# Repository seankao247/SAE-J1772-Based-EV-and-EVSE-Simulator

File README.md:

# still working on it
Referenced from https://github.com/OpenEVSE

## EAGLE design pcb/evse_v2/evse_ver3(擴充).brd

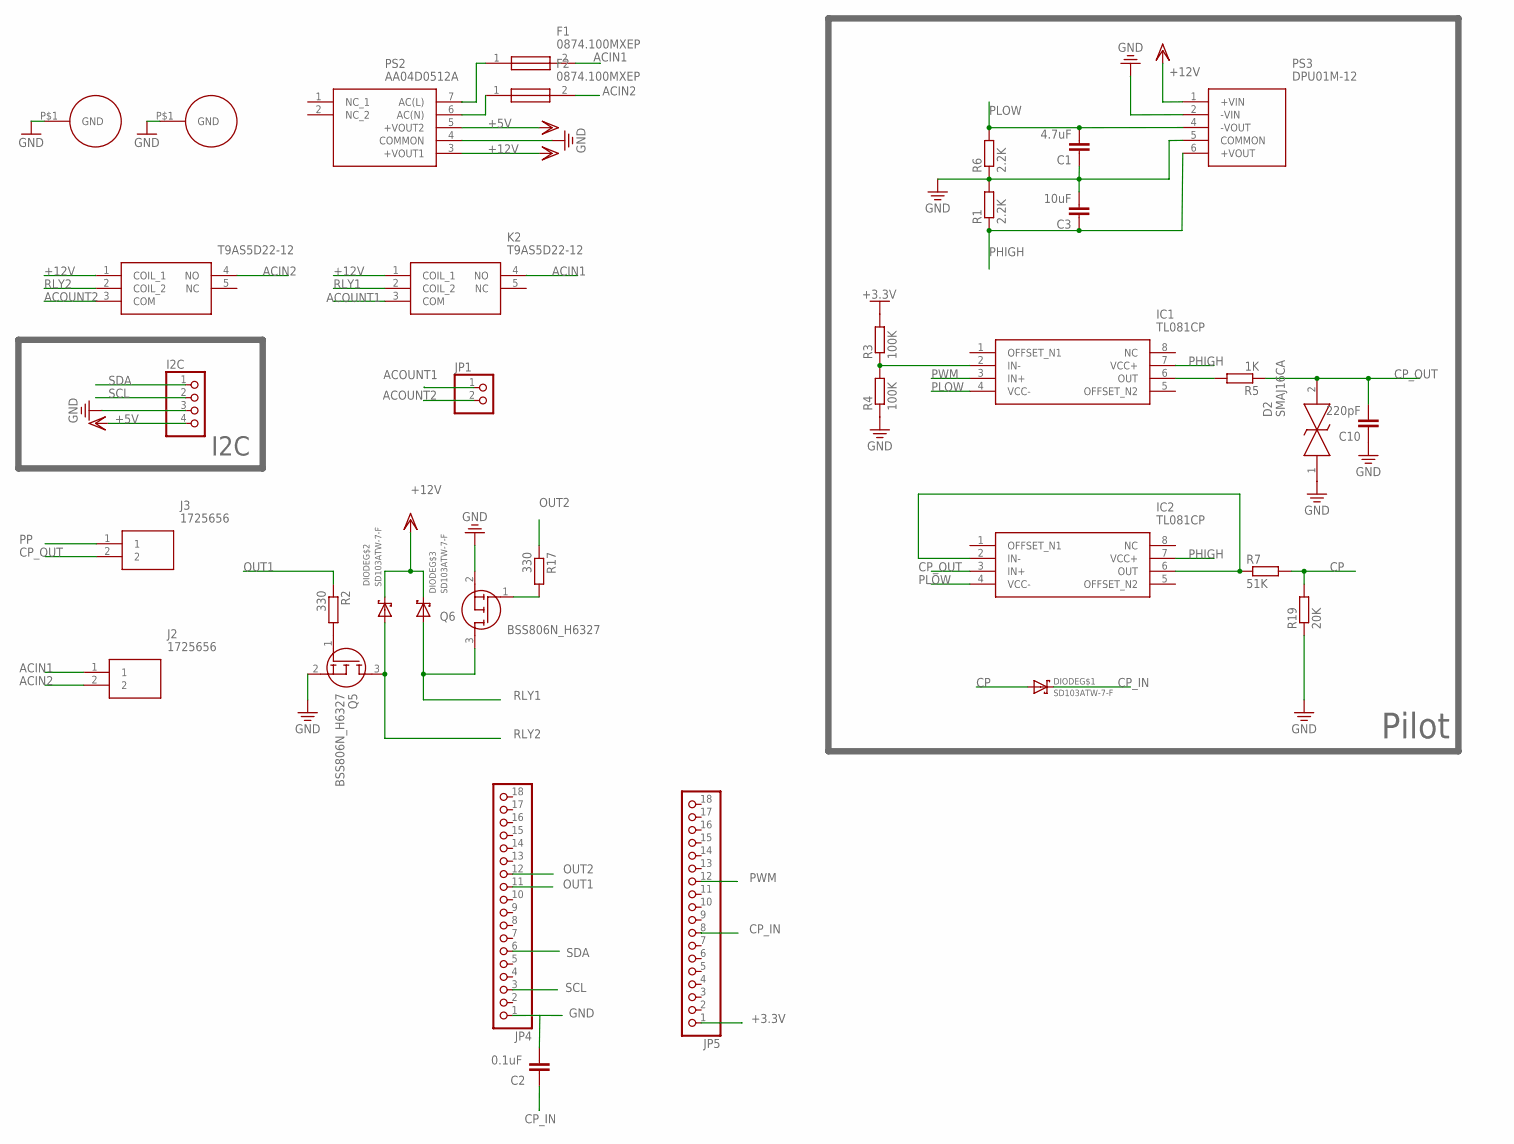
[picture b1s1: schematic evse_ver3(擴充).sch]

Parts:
C1: 4.7uF; C0805
C2: 0.1uF; C0805
C3: 10uF; C0805
C10: 220pF; C0805
D2: SMAJ16CA; DIOM6626X229N
DIODE: SD103ATW-7-F; SOT363
F1, F2: 0874.100MXEP; 0874100MXEP
I2C: PINHD-1X4; 1X04
IC1, IC2: TL081CP; DIP794W53P254L959H508Q8N
J2, J3: 1725656
JP1: PINHD-1X2; 1X02
JP4, JP5: PINHD-1X18; 1X18
K2, K3: T9AS5D22-12; T9AS5D2224314191046
PS2: AA04D0512A
PS3: DPU01M-12; DPU01M12
Q5, Q6: BSS806N_H6327; SOT95P240X110-3N
R1, R6: 2.2K; R0805
R2, R17: 330; R0805
R3, R4: 100K; R0805
R5: 1K; R0805
R7: 51K; R0805
R19: 20K; R0805
U$3, U$4: HOLE

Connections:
+3.3V: JP5.1, R3.2
+5V: I2C.4, PS2.5 (+VOUT2)
+12V: DIODE.2 (C), DIODE.3 (C), K2.1 (COIL_1), K3.1 (COIL_1), PS2.3 (+VOUT1), PS3.1 (+VIN)
ACIN1: F1.2, J2.1, K2.4 (NO)
ACIN2: F2.2, J2.2, K3.4 (NO)
ACOUNT1: JP1.1, K2.3 (COM)
ACOUNT2: JP1.2, K3.3 (COM)
CP: DIODE.6 (A), R7.2, R19.2
CP_IN: C2.1, DIODE.1 (C), JP5.8
CP_OUT: C10.2, D2.2, IC2.3 (IN+), J3.2, R5.1
GND: C1.1, C2.2, C3.2, C10.1, D2.1, I2C.3, JP4.1, PS2.4 (COMMON), PS3.2 (-VIN), PS3.5 (COMMON), Q5.2 (S), Q6.2 (S), R1.2, R4.1, R6.1, R19.1, U$3.P$1, U$4.P$1
unnamed: IC1.2 (IN-), R3.1, R4.2
unnamed: IC1.6 (OUT), R5.2
unnamed: Q5.1 (G), R2.2
unnamed: Q6.1 (G), R17.2
unnamed: IC2.2 (IN-), IC2.6 (OUT), R7.1
unnamed: F2.1, PS2.6 (AC(N))
unnamed: F1.1, PS2.7 (AC(L))
OUT1: JP4.11, R2.1
OUT2: JP4.12, R17.1
PHIGH: C3.1, IC1.7 (VCC+), IC2.7 (VCC+), PS3.6 (+VOUT), R1.1
PLOW: C1.2, IC1.4 (VCC-), IC2.4 (VCC-), PS3.4 (-VOUT), R6.2
PP: J3.1
PWM: IC1.3 (IN+), JP5.12
RLY1: DIODE.4 (A), K2.2 (COIL_2), Q6.3 (D)
RLY2: DIODE.5 (A), K3.2 (COIL_2), Q5.3 (D)
SCL: I2C.2, JP4.3
SDA: I2C.1, JP4.6

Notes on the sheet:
Pilot
I2C

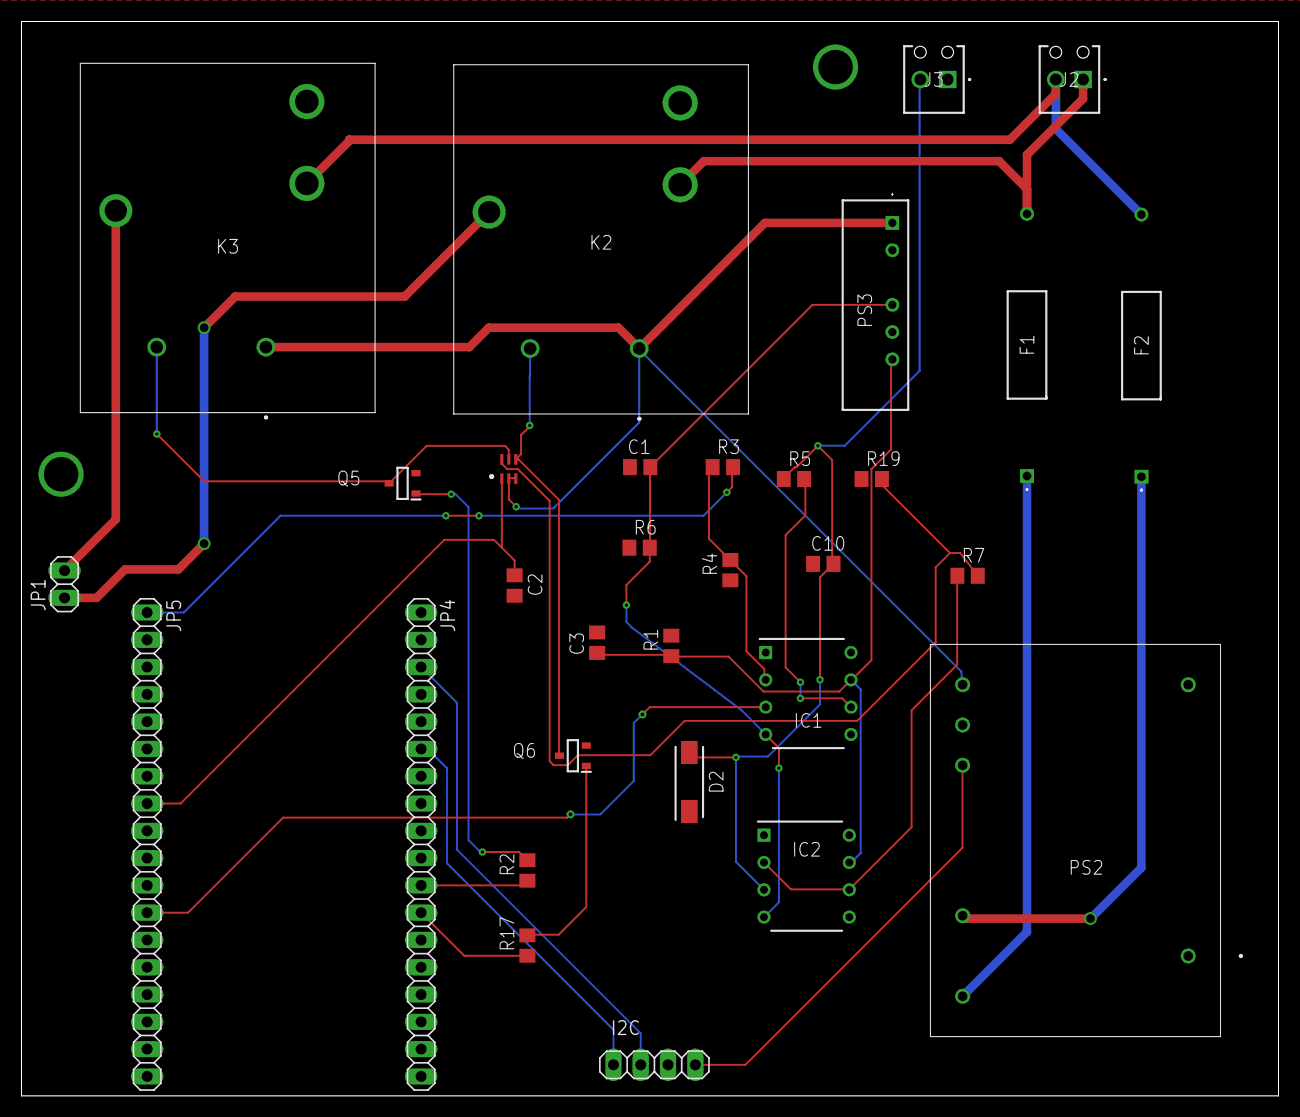
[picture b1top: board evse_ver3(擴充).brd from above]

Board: 2 copper layers, 117.0 x 100.0 mm, 33 parts (0 on the bottom side), 27 nets.

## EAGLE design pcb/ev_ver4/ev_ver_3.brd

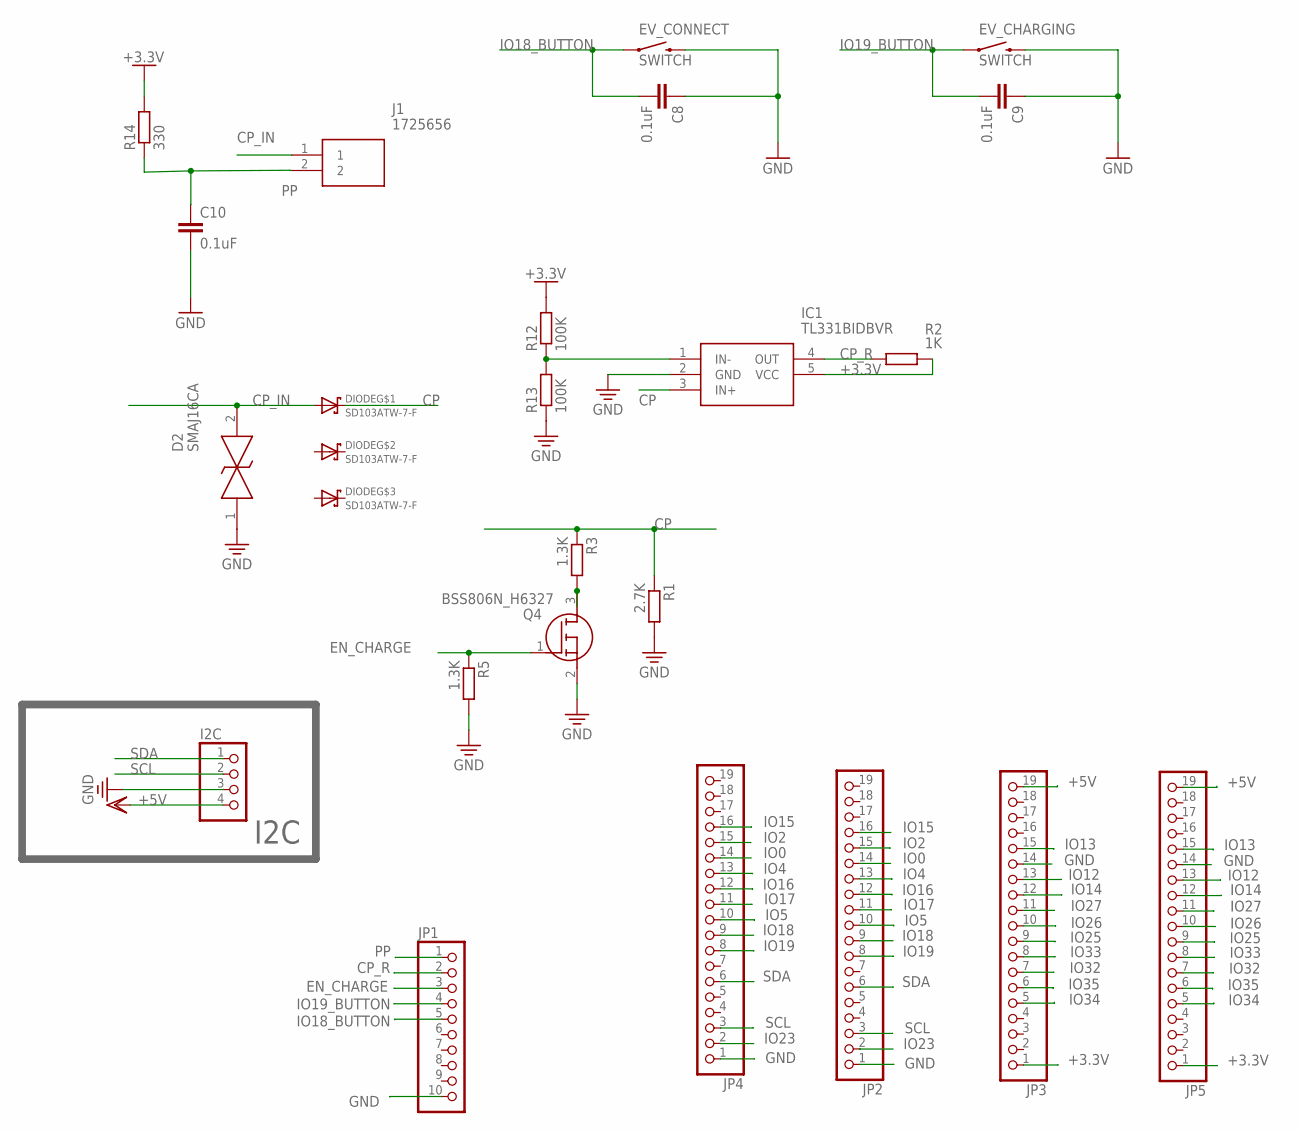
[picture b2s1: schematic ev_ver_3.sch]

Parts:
C8, C9, C10: 0.1uF; C0805
D2: SMAJ16CA; DIOM6626X229N
DIODE: SD103ATW-7-F; SOT363
EV_CHARGING: SWITCH; SWITCH_2PIN
EV_CONNECT: SWITCH; SWITCH_2PIN
I2C: PINHD-1X4; 1X04
IC1: TL331BIDBVR; SOT95P280X145-5N
J1: 1725656
JP1: PINHD-1X10; 1X10
JP2, JP3, JP4, JP5: PINHD-1X19; 1X19
Q4: BSS806N_H6327; SOT95P240X110-3N
R1: 2.7K; R0805
R2: 1K; R0805
R3, R5: 1.3K; R0805
R12, R13: 100K; R0805
R14: 330; R0805

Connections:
+3.3V: IC1.5 (VCC), JP3.1, JP5.1, R2.2, R12.2, R14.2
+5V: I2C.4, JP3.19, JP5.19
CP: DIODE.1 (C), IC1.3 (IN+), R1.1, R3.1
CP_IN: D2.2, DIODE.6 (A), J1.1
CP_R: IC1.4 (OUT), JP1.2, R2.1
EN_CHARGE: JP1.3, Q4.1 (G), R5.1
GND: C8.1, C9.1, C10.2, D2.1, EV_CHARGING.2, EV_CONNECT.2, I2C.3, IC1.2 (GND), JP1.10, JP2.1, JP3.14, JP4.1, JP5.14, Q4.2 (S), R1.2, R5.2, R13.1
IO0: JP2.14, JP4.14
IO2: JP2.15, JP4.15
IO4: JP2.13, JP4.13
IO5: JP2.10, JP4.10
IO12: JP3.13, JP5.13
IO13: JP3.15, JP5.15
IO14: JP3.12, JP5.12
IO15: JP2.16, JP4.16
IO16: JP2.12, JP4.12
IO17: JP2.11, JP4.11
IO18: JP2.9, JP4.9
IO18_BUTTON: C8.2, EV_CONNECT.1, JP1.5
IO19: JP2.8, JP4.8
IO19_BUTTON: C9.2, EV_CHARGING.1, JP1.4
IO23: JP2.2, JP4.2
IO25: JP3.9, JP5.9
IO26: JP3.10, JP5.10
IO27: JP3.11, JP5.11
IO32: JP3.7, JP5.7
IO33: JP3.8, JP5.8
IO34: JP3.5, JP5.5
IO35: JP3.6, JP5.6
unnamed: Q4.3 (D), R3.2
unnamed: IC1.1 (IN-), R12.1, R13.2
PP: C10.1, J1.2, JP1.1, R14.1
SCL: I2C.2, JP2.3, JP4.3
SDA: I2C.1, JP2.6, JP4.6

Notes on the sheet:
I2C

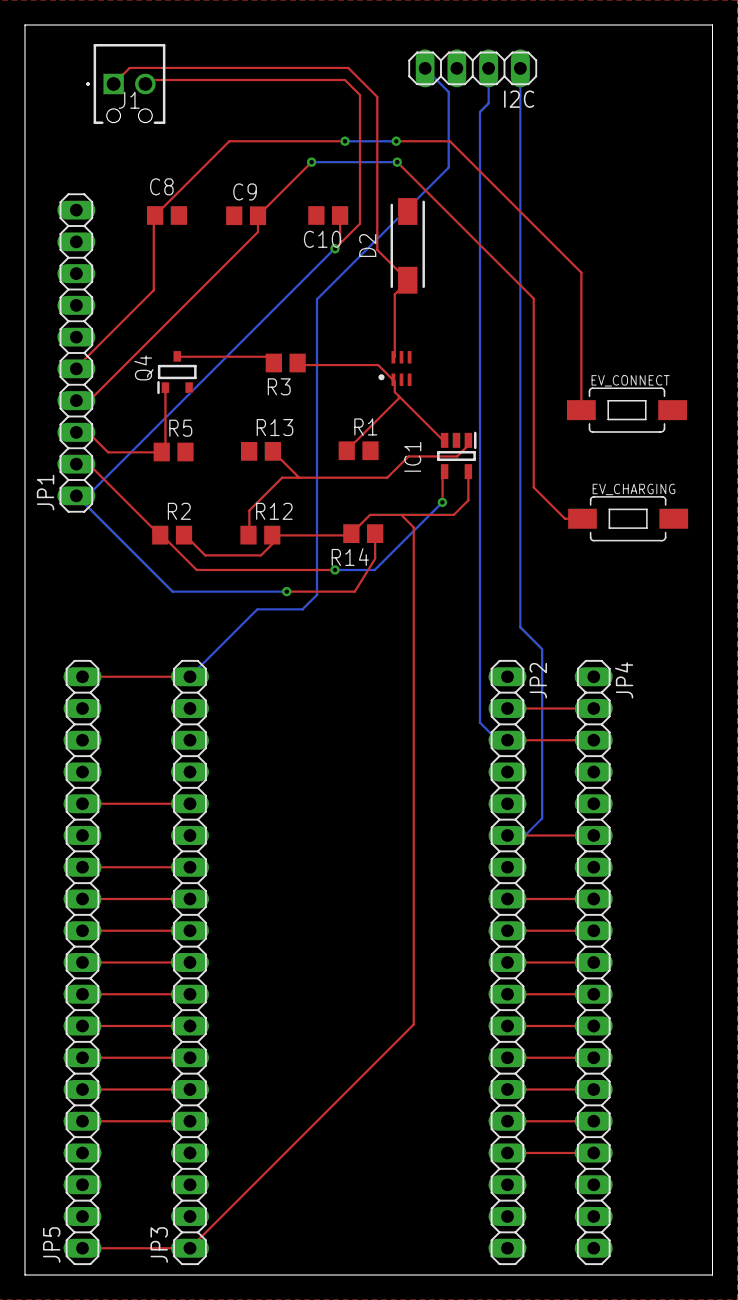
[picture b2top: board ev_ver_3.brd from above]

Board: 2 copper layers, 55.0 x 100.0 mm, 23 parts (0 on the bottom side), 34 nets.
